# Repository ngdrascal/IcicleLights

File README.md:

# IcicleLights
A remix of "Adafruit's Holiday Icicle Lights with Flair" build.

<h3>Controller PCB<h3>

<h3>Spat Strand PCB<h3>

<h3>Drip Strand PCB<h3>

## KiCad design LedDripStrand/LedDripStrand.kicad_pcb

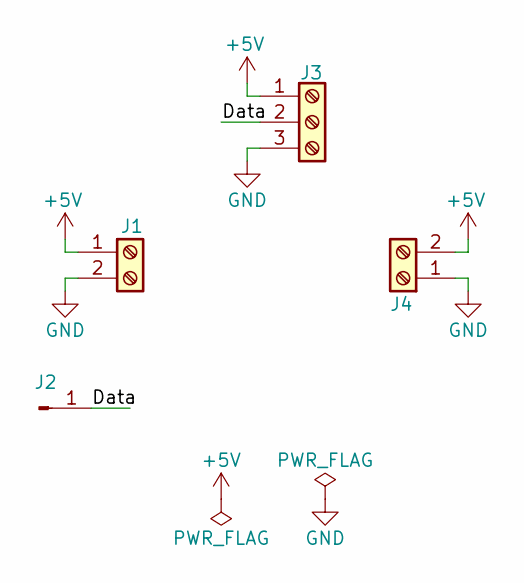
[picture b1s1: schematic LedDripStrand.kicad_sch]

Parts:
J1, J4: Screw_Terminal_01x02; PHOENIX - TERM BLK 2P SIDE ENT 5.08MM PCB; DigiKey Part 277-1247-ND
J2: Conn_01x01_Pin; PinHeader_1x01_P2.54mm_Vertical
J3: Screw_Terminal_01x03; PHOENIX - TERM BLK 3P SIDE ENT 5.08MM PCB; DigiKey Part 277-1248-ND

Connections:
+5V: J1.1, J3.1, J4.2
/Data: J2.1, J3.2
GND: J1.2, J3.3, J4.1

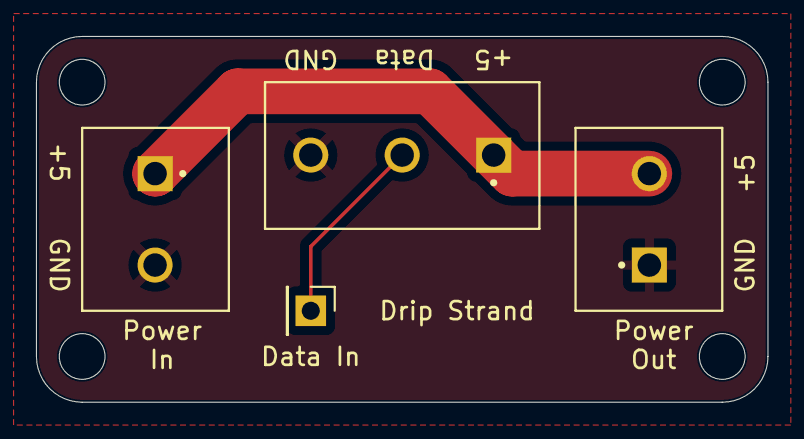
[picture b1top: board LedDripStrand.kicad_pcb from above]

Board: 2 copper layers, 40.6 x 20.3 mm, 4 parts (0 on the bottom side), 3 nets.

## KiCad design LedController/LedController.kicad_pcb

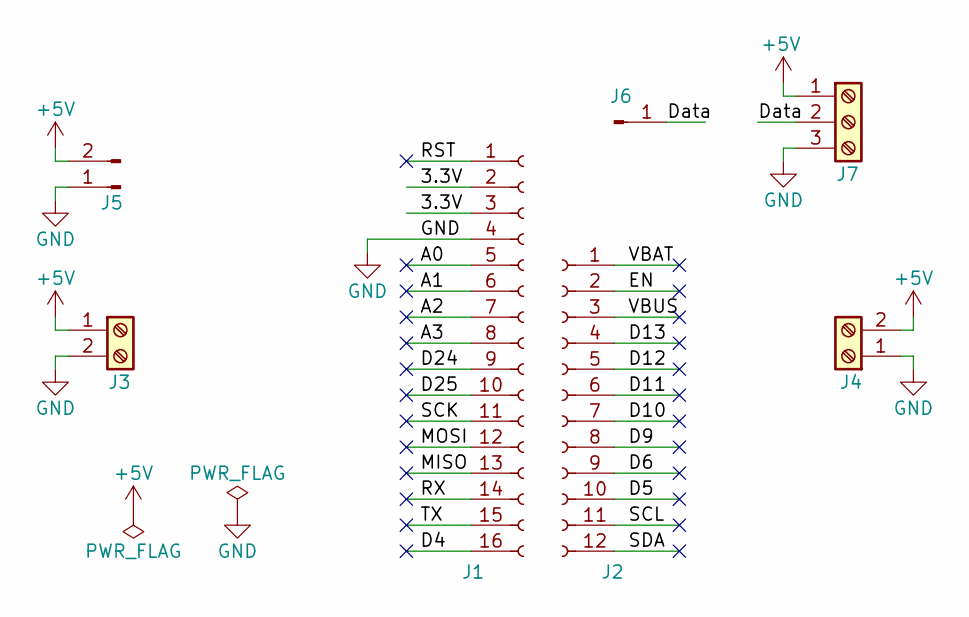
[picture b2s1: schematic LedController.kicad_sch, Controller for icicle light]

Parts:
J1: Conn_01x16_Socket; PinSocket_1x16_P2.54mm_Vertical
J2: Conn_01x12_Female; PinSocket_1x12_P2.54mm_Vertical
J3, J4: Screw_Terminal_01x02; PHOENIX - TERM BLK 2P SIDE ENT 5.08MM PCB; DigiKey Part 277-1247-ND
J5: Conn_01x02_Pin; SolderWire-0.5sqmm_1x02_P4.6mm_D0.9mm_OD2.1mm
J6: Conn_01x01_Pin; PinHeader_1x01_P2.54mm_Vertical
J7: Screw_Terminal_01x03; PHOENIX - TERM BLK 3P SIDE ENT 5.08MM PCB; DigiKey Part 277-1248-ND

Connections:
+5V: J3.1, J4.2, J5.2, J7.1
/3.3V: J1.2, J1.3
/A0: J1.5
/A1: J1.6
/A2: J1.7
/A3: J1.8
/D4: J1.16
/D5: J2.10
/D6: J2.9
/D9: J2.8
/D10: J2.7
/D11: J2.6
/D12: J2.5
/D13: J2.4
/D24: J1.9
/D25: J1.10
/Data: J6.1, J7.2
/EN: J2.2
/MISO: J1.13
/MOSI: J1.12
/RST: J1.1
/RX: J1.14
/SCK: J1.11
/SCL: J2.11
/SDA: J2.12
/TX: J1.15
/VBAT: J2.1
/VBUS: J2.3
GND: J1.4, J3.2, J4.1, J5.1, J7.3

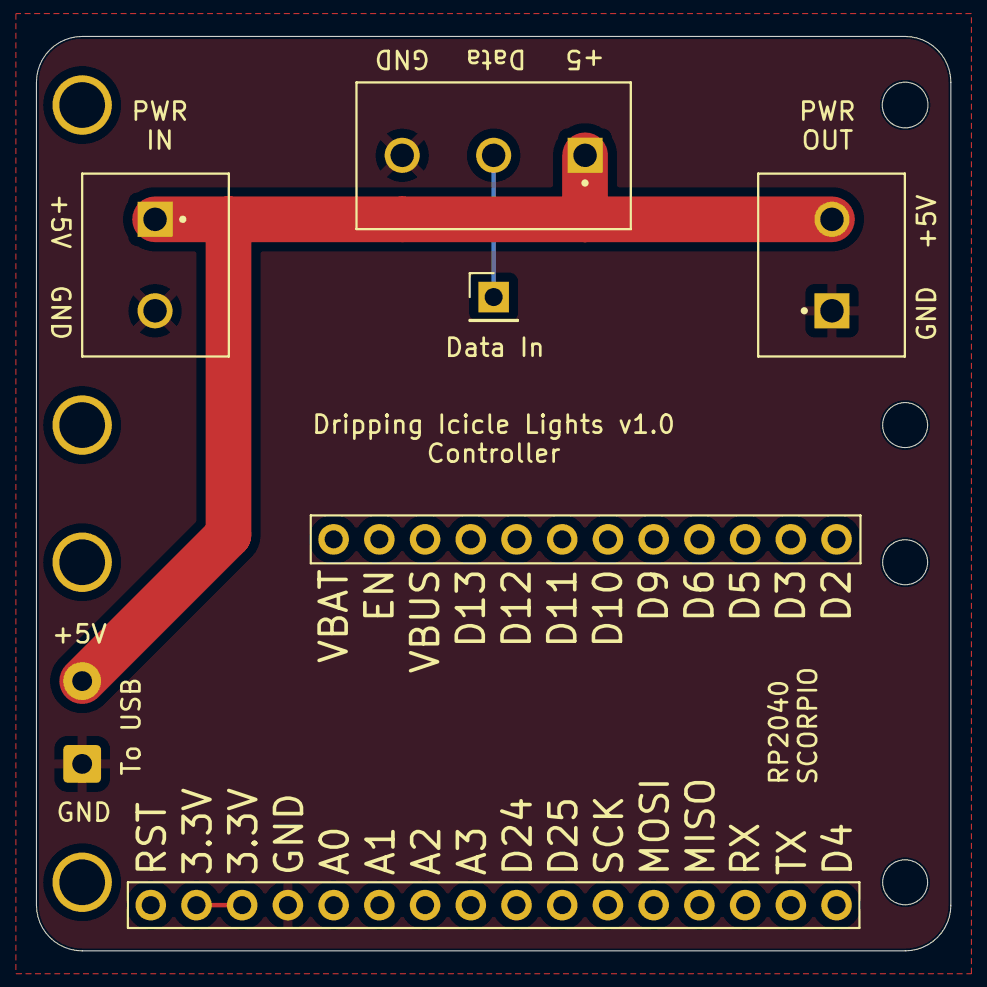
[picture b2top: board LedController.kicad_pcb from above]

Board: 2 copper layers, 50.8 x 50.8 mm, 7 parts (0 on the bottom side), 4 nets.

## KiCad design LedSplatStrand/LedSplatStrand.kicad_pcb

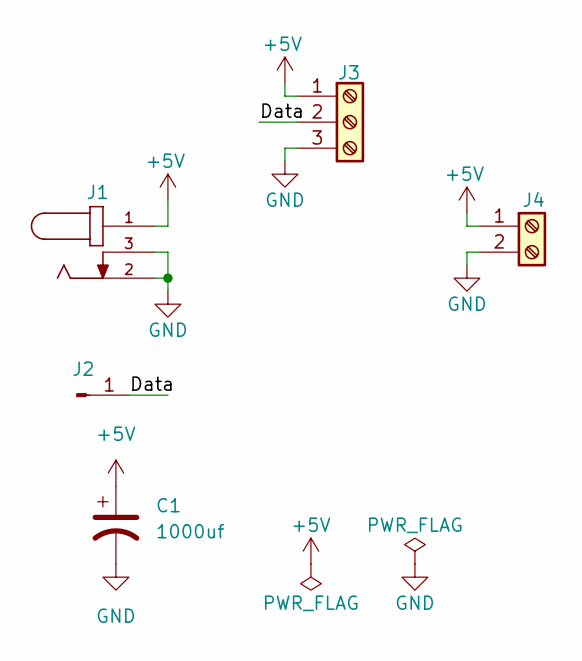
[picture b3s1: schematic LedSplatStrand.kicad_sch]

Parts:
C1: 1000uf; CP_Radial_D10.0mm_P5.00mm; DigiKey Part 1189-1583-1-ND
J1: PJ-102B; CUI_PJ-102B; PART_REV 1.03; DigiKey Part CP-102B-ND
J2: Conn_01x01_Pin; PinHeader_1x01_P2.54mm_Vertical
J3: Screw_Terminal_01x03; PHOENIX - TERM BLK 3P SIDE ENT 5.08MM PCB; DigiKey Part 277-1248-ND
J4: Screw_Terminal_01x02; PHOENIX - TERM BLK 2P SIDE ENT 5.08MM PCB; DigiKey Part 277-1247-ND

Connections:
+5V: C1.1, J1.1, J3.1, J4.1
/Data: J2.1, J3.2
GND: C1.2, J1.2, J1.3, J3.3, J4.2

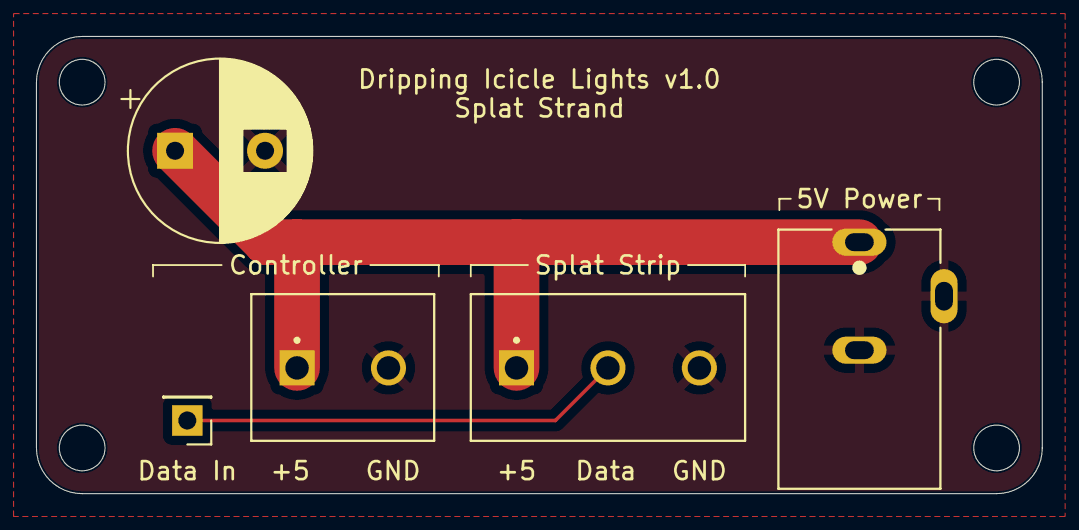
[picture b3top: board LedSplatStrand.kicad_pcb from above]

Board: 2 copper layers, 55.9 x 25.4 mm, 5 parts (0 on the bottom side), 3 nets.

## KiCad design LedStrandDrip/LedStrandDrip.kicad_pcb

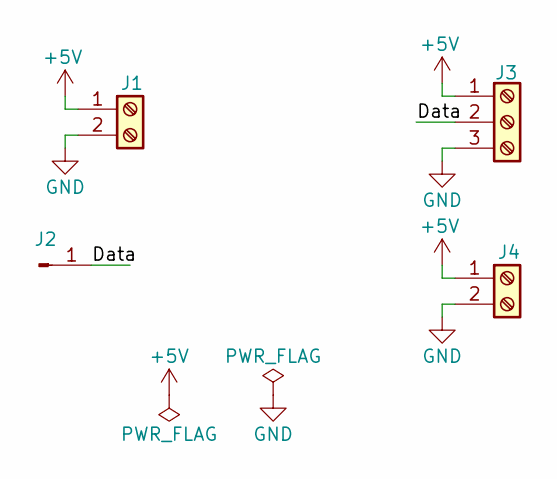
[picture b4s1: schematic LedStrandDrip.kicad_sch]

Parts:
J1, J4: Screw_Terminal_01x02; PHOENIX - TERM BLK 2P SIDE ENT 5.08MM PCB; DigiKey Part 277-1247-ND
J2: Conn_01x01_Pin; PinHeader_1x01_P2.54mm_Vertical
J3: Screw_Terminal_01x03; PHOENIX - TERM BLK 3P SIDE ENT 5.08MM PCB; DigiKey Part 277-1248-ND

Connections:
+5V: J1.1, J3.1, J4.1
/Data: J2.1, J3.2
GND: J1.2, J3.3, J4.2

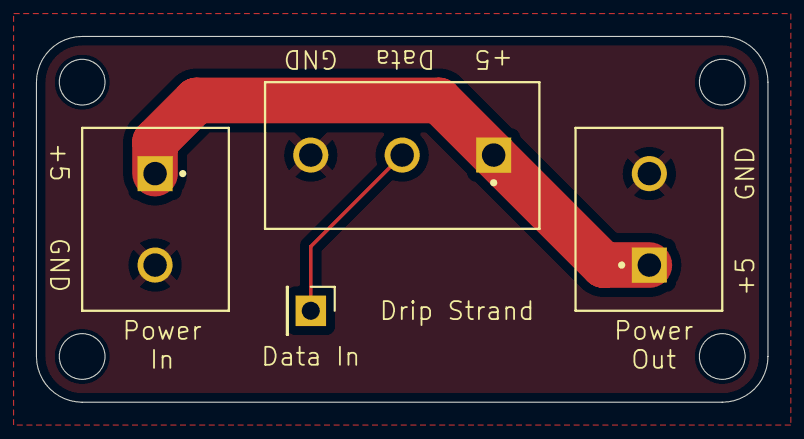
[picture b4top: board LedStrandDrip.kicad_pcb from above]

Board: 2 copper layers, 40.6 x 20.3 mm, 4 parts (0 on the bottom side), 3 nets.

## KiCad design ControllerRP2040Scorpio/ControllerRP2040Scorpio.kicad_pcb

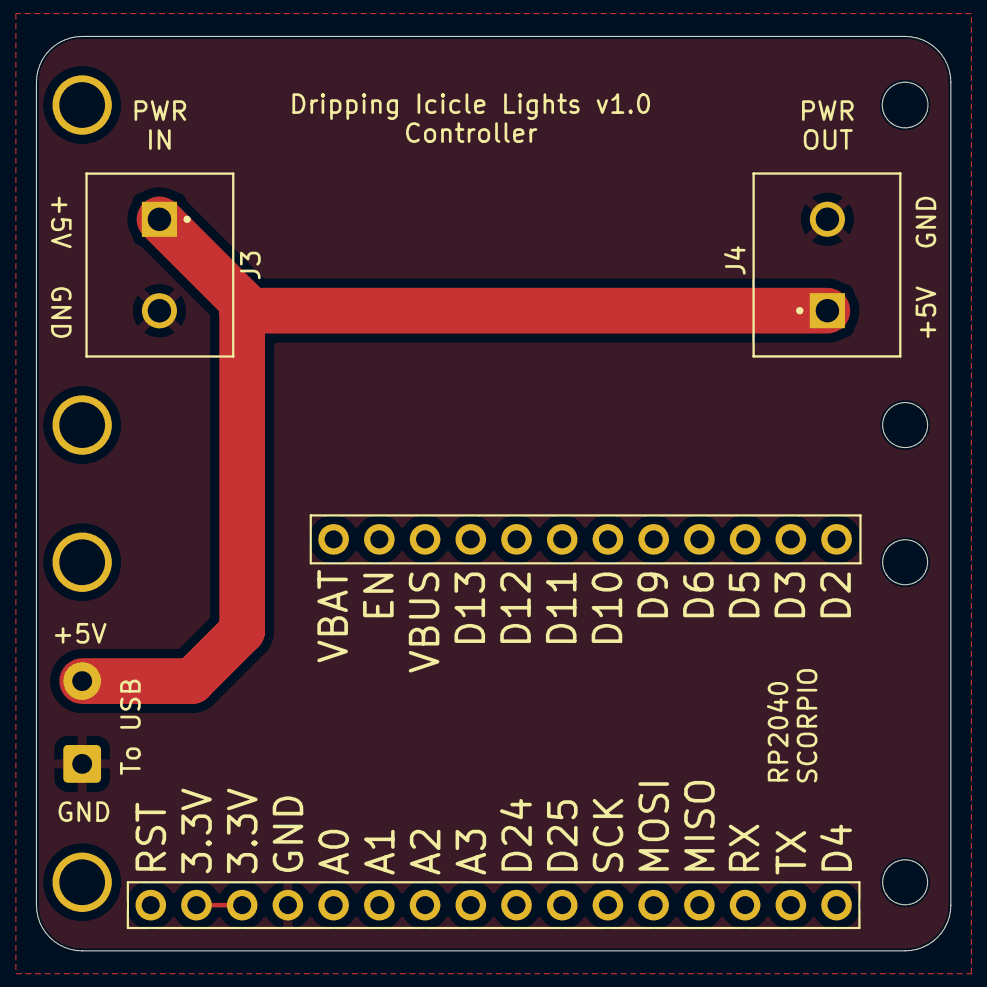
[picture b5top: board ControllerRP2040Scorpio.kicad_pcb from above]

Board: 2 copper layers, 50.8 x 50.8 mm, 5 parts (0 on the bottom side), 3 nets.

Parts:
J1: Conn_01x16_Socket; PinSocket_1x16_P2.54mm_Vertical
J2: Conn_01x12_Female; PinSocket_1x12_P2.54mm_Vertical
J3, J4: Screw_Terminal_01x02; PHOENIX - TERM BLK 2P SIDE ENT 5.08MM PCB
J5: Conn_01x02_Pin; SolderWire-0.5sqmm_1x02_P4.6mm_D0.9mm_OD2.1mm

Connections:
+5V: J3.1, J4.1, J5.2
/3.3V: J1.2, J1.3
GND: J1.4, J3.2, J4.2, J5.1

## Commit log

2025-01-05 incremental updates
2025-01-11 incremetal updates
